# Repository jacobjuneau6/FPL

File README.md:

# FPL
FPL is a FPGA based board that runs linux and provides many digital interfaces.
# WHY
I have always wanted to have a benchtop device that can probe I2C,SPI and uart devices all ath the same time. In addition, I have always wanted to mess around with and use an FPGA.
# PCB

# BOM
| Name | Purpose | Quantity | Total Cost (USD) | Link | Distributor |
| --- | --- | --- | --- | --- | --- |
| 50g Solder Paste | To solder the componets to the board | 1 | 7.34 | https://www.aliexpress.com/item/3256809620386958.html?spm=a2g0o.cart.0.0.202b38daefHo7C&mp=1&pdp_npi=6%40dis%21USD%21USD%2015.29%21USD%207.34%21%21USD%207.34%21%21%21%402103129f17757943610901426e699a%2112000050236831009%21ct%21US%216291447553%21%211%210%21 | Aliexpres |
| FT232H USB -> Bridge | allows programming and debugging the fpga before the core starts | 1 | 7.72 | https://www.aliexpress.com/item/3256810218473690.html?spm=a2g0o.cart.0.0.202b38daefHo7C&mp=1&pdp_npi=6%40dis%21USD%21USD%2015.44%21USD%207.72%21%21USD%207.72%21%21%21%402103129f17757943610901426e699a%2112000052298998974%21ct%21US%216291447553%21%211%210%21 | Aliexpress |
| M-F Dupont Cable | to connect debugger and peripherals | 1 | 2.27 | https://www.aliexpress.com/item/3256803454873245.html?spm=a2g0o.cart.0.0.202b38daefHo7C&mp=1&pdp_npi=6%40dis%21USD%21USD%202.28%21USD%202.27%21%21USD%202.27%21%21%21%402103129f17757943610901426e699a%2112000026613929403%21ct%21US%216291447553%21%211%210%21&pdp_ext_f=%7B%22cart2PdpParams%22%3A%7B%22pdpBusinessMode%22%3A%22retail%22%7D%7D | Aliexpress |
| F-F dupont cable | to wire up debugger and peripherals | 1 | 2.06 | https://www.aliexpress.com/item/3256803454873245.html?spm=a2g0o.cart.0.0.202b38daefHo7C&mp=1&pdp_npi=6%40dis%21USD%21USD%202.07%21USD%202.06%21%21USD%202.06%21%21%21%402103129f17757943610901426e699a%2112000026613929398%21ct%21US%216291447553%21%211%210%21&pdp_ext_f=%7B%22cart2PdpParams%22%3A%7B%22pdpBusinessMode%22%3A%22retail%22%7D%7D | Aliexpress |
| solder paste scraper | to apply the solder paste | 5 | 3.61 | https://www.aliexpress.com/item/3256807243226858.html?spm=a2g0o.cart.0.0.202b38daefHo7C&mp=1&pdp_npi=6%40dis%21USD%21USD%203.61%21USD%203.61%21%21USD%203.61%21%21%21%402103129f17757943610901426e699a%2112000056533716799%21ct%21US%216291447553%21%211%210%21 | Aliexpress |
| JLCPCB Stencils | to make assembly easier | 2 | 6.09 |  | JLCPCB |
| JLCPCB PCBs | Holds all components | 5 | 7.00 |  | JLCPCB |
| MicroSD card holder | storage | 1 | 1.57 | https://www.digikey.com/en/products/detail/hirose-electric-co-ltd/DM3CS-SF/2602739?s=N4IgTCBcDaIBICUCMBOA7GAwgFQLQDkAREAXQF8g | Digikey |
| USB-C connector | data transfer | 1 | 2.99 | https://www.digikey.com/en/products/detail/hirose-electric-co-ltd/CX90BW1-24P1/22566049?s=N4IgTCBcDa4GwFoDCANAnABgEIHUCMCYALAAp5IAqCAcgCIgC6AvkA | Digikey |
| Ethernet Jack | data transfer | 1 | 4.42 | https://www.digikey.com/en/products/detail/te-connectivity-amp-connectors/2041411-1/7039302?s=N4IgTCBcDaIIIEYDMBWAbKgwgFQLQDkAREAXQF8g | Digikey |
| Mosfet | reset the sd card | 1 | 0.28 | https://www.digikey.com/en/products/detail/infineon-technologies/BSS84PH6327XTSA2/5413661?s=N4IgTCBcDaIEIGUEA4AsAFAEgNgMxgHYANAFQQEEwBhEgWgDkAREAXQF8g | Digikey |
| 10K resistors | filtering | 18 | 0.00 |  |  |
| 5.1K resistors | filtering | 2 | 0.20 | https://www.digikey.com/en/products/detail/yageo/RC0402FR-075K1L/726624?s=N4IgTCBcDaIMwEYEFoCsA6BAGA0gGQCUBhAFWQDkAREAXQF8g | Digikey |
| Infineon S80KS5123GABHV020 | RAM | 1 | 11.59 | https://www.digikey.com/en/products/detail/infineon-technologies/S80KS5123GABHV020/15965285 | Digikey |
| tactile button | fpga reset | 1 | 0.24 | https://www.digikey.com/en/products/detail/omron-electronics-inc-emc-div/B3F-1000/33150 | Digikey |
| Dip switches | fpga confiuration | 1 | 3.41 | https://www.digikey.com/en/products/detail/w%C3%BCrth-elektronik/416131160803/3174527?s=N4IgTCBcDaIOwGYwFoAsBGAbOh6sAYAOfBAYQBVkA5AERAF0BfIA | Digikey |
| FPGA | main chip | 1 | 21.78 | https://www.digikey.com/en/products/detail/lattice-semiconductor-corporation/LFE5U-25F-6BG256C/9553918 | Digikey |
| Ethernet Interface | data transfer | 1 | 1.03 | https://www.digikey.com/en/products/detail/microchip-technology/LAN8720A-CP-TR/3872109 | Digikey |
| 1V2 LDO | power regulation | 1 | 0.39 | https://www.digikey.com/en/products/detail/stmicroelectronics/LD1117S12CTR/1880164?s=N4IgTCBcDaIDIBECMKDsBlJYDCAVASiALoC%2BQA | Digikey |
| CP2102 | usb>uart | 1 | 4.14 | https://www.digikey.com/en/products/detail/silicon-labs/CP2102N-A02-GQFN24R/9863479?s=N4IgTCBcDaIMxwGwFoCsAOTyCMyByAIiALoC%2BQA | Digikey |
| SPI Flash | storage | 1 | 2.31 | https://www.digikey.com/en/products/detail/winbond-electronics/W25Q128JVSIQ-TR/5803944?s=N4IgTCBcDa4KwDYC0B1McCKBGMAOAUgGoDKAkhgCoBKAwhUgHIAiIAugL5A | Digikey |
| 25MHZ clock | clock | 1 | 0.99 | https://www.digikey.com/en/products/detail/abracon-llc/ASE-25-000MHZ-L-C-T/1236885?s=N4IgTCBcDaIKwGY4FoCCBlAosscB0ADEQLIASAWsgDLIDCyAKrQ8gHIAiIAugL5A | Digikey |
| 25MHZ Parrallel clock | ethernet | 1 | 1.02 | https://www.digikey.com/en/products/detail/ecs-inc/ECS-250-18-23A-EN-TR/2213748?s=N4IgTCBcDaIBoGECMA2A7EhAVAtAOQBEQBdAXyA | Digikey |
| 4.7K resistors | filtering | 3 | 0.30 | https://www.digikey.com/en/products/detail/yageo/RC0402JR-074K7L/726477?s=N4IgTCBcDaIMwEYEFoAsA6A7AaQFICUBhAFWQDkAREAXQF8g | Digikey |
| 0.1uF capacitor | power filtering | 4 | 0.32 | https://www.digikey.com/en/products/detail/murata-electronics/GRM022D80G104ME15L/5027471?s=N4IgTCBcDaICwE4AMBaAjEgzADgGzpQDkAREAXQF8g | Digikey |
| 22pF capacitor | power filtering | 2 | 0.16 | https://www.digikey.com/en/products/detail/yageo/CC0402JRNPO9BN220/302752 | Digikey |
| 3V3 LDO | power regulation | 1 | 0.32 | https://www.digikey.com/en/products/detail/stmicroelectronics/LD1117S33CTR/585765?s=N4IgTCBcDaIDIBECMKDsBlAzJgwgFQCUQBdAXyA | Digikey |
| 2V5 LDO | power regulation | 1 | 0.49 | https://www.digikey.com/en/products/detail/stmicroelectronics/LD1117S25CTR/585764?s=N4IgTCBcDaIDIBECMKDsBlMBWAwgFQCUQBdAXyA | Digikey |
| 1V8 LDO | power regulation | 1 | 0.42 | https://www.digikey.com/en/products/detail/stmicroelectronics/LD1117S18TR/1038359?s=N4IgTCBcDaIDIBECMKDsBlJAOAKgJRAF0BfIA | Digikey |
| green LED | indication light | 2 | 0.54 | https://www.digikey.com/en/products/detail/w%C3%BCrth-elektronik/155124GS73200A/8557187?s=N4IgTCBcDaIOwGYwFoCMYAMYWuQOQBEQBdAXyA | Digikey |

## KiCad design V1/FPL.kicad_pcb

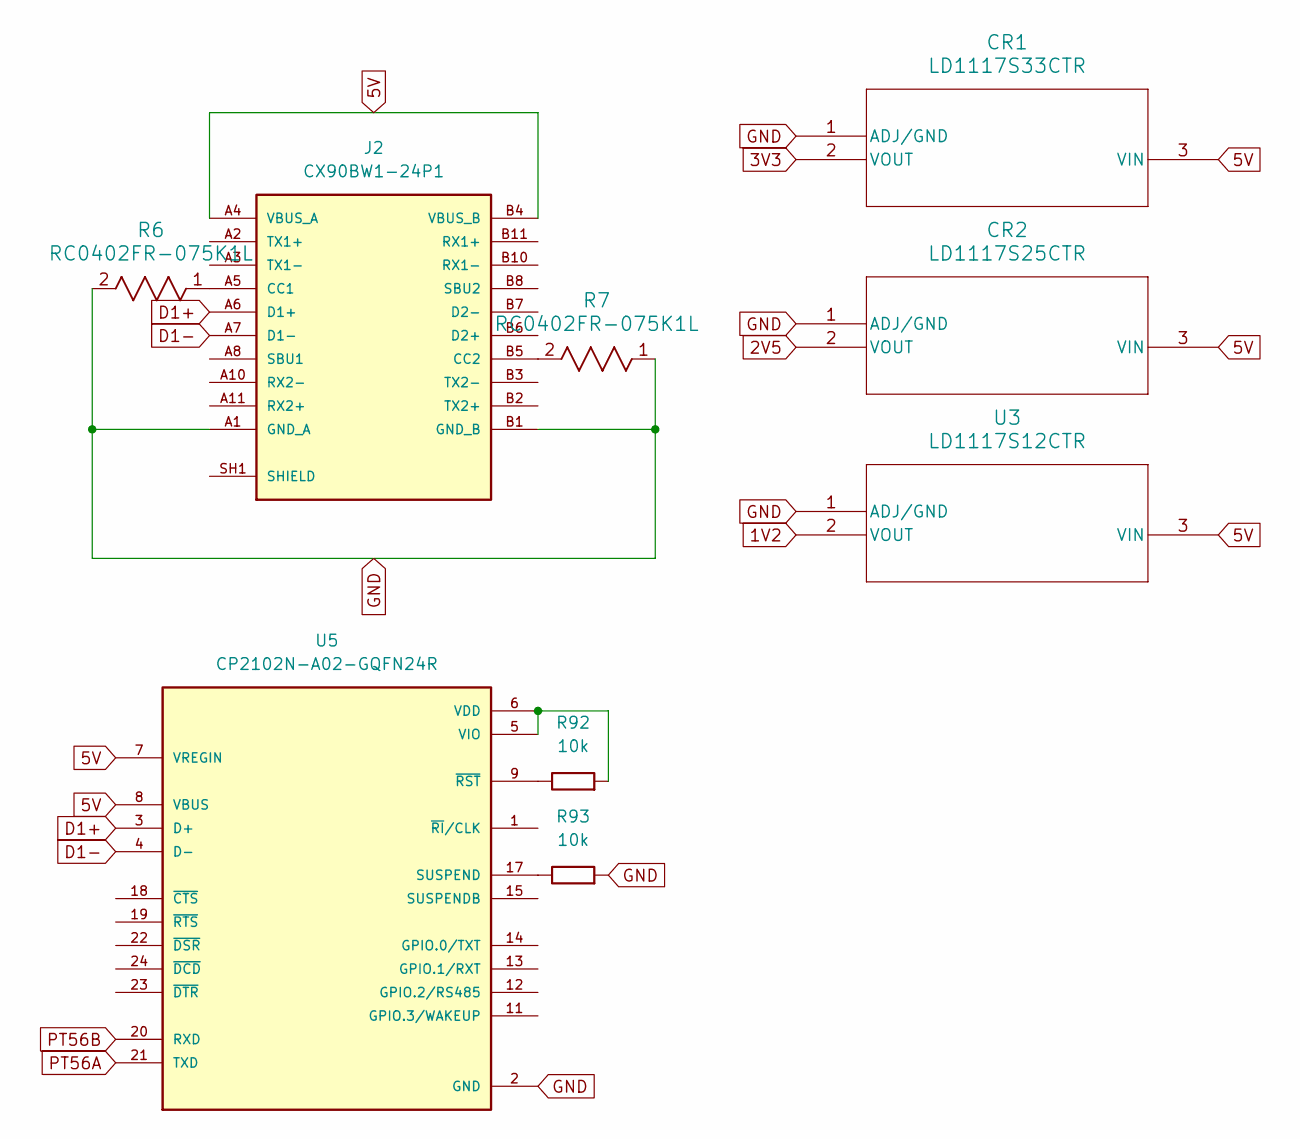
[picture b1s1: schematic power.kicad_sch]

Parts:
CR1: LD1117S33CTR; SOT-223_STM; DigiKey_Part_Number LD1117S33CTR
CR2: LD1117S25CTR; SOT-223_STM; DigiKey_Part_Number LD1117S25CTR
J2: CX90BW1-24P1; HIROSE_CX90BW1-24P1; PARTREV 24.05.01; DigiKey_Part_Number 26-CX90BW1-24P1CT-ND
R6, R7: RC0402FR-075K1L; RC0402N_YAG; DigiKey_Part_Number 311-5.10KLRCT-ND
R92, R93: 10k; R_Axial_DIN0207_L6.3mm_D2.5mm_P10.16mm_Horizontal; DigiKey_Part_Number N/A
U3: LD1117S12CTR; SOT-223_STM; DigiKey_Part_Number LD1117S12CTR
U5: CP2102N-A02-GQFN24R; QFN50P400X400X80-25N; PARTREV 1.3; DigiKey_Part_Number 336-5888-1-ND

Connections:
1V2: U3.2 (VOUT); also elsewhere on the board
2V5: CR2.2 (VOUT); also elsewhere on the board
3V3: CR1.2 (VOUT); also elsewhere on the board
5V: CR1.3 (VIN), CR2.3 (VIN), J2.A4 (VBUS_A), J2.A9 (VBUS_A), J2.B4 (VBUS_B), J2.B9 (VBUS_B), U3.3 (VIN), U5.7 (VREGIN), U5.8 (VBUS); also elsewhere on the board
D1+: J2.A6 (D1+), U5.3 (D+)
D1-: J2.A7 (D1-), U5.4 (D-)
GND: CR1.1 (ADJ/GND), CR2.1 (ADJ/GND), J2.A1 (GND_A), J2.A12 (GND_A), J2.B1 (GND_B), J2.B12 (GND_B), R6.2, R7.1, R93.1, U3.1 (ADJ/GND), U5.2 (GND), U5.25 (GND); also elsewhere on the board
unnamed: J2.A5 (CC1), R6.1
unnamed: J2.B5 (CC2), R7.2
unnamed: J2.SH1 (SHIELD), J2.SH2 (SHIELD), J2.SH3 (SHIELD), J2.SH4 (SHIELD)
unnamed: R93.2, U5.17 (SUSPEND)
unnamed: R92.1, U5.5 (VIO), U5.6 (VDD)
unnamed: R92.2, U5.9 (~RST)
PT56A: U5.21 (TXD); also elsewhere on the board
PT56B: U5.20 (RXD); also elsewhere on the board

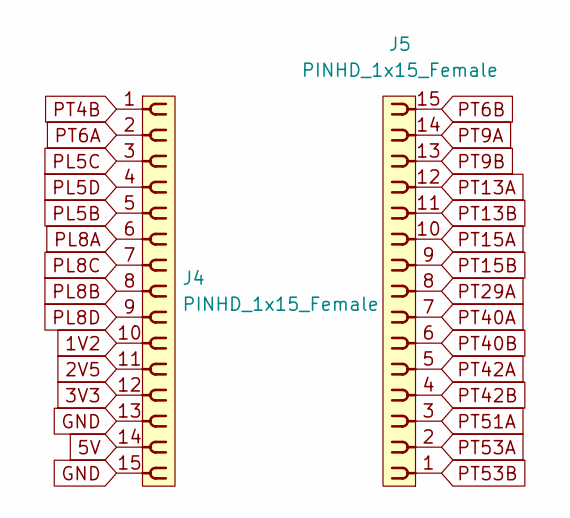
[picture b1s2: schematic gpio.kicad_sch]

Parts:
J4, J5: PINHD_1x15_Female; PinSocket_1x15_P2.54mm_Vertical

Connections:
1V2: J4.10; also elsewhere on the board
2V5: J4.11; also elsewhere on the board
3V3: J4.12; also elsewhere on the board
5V: J4.14; also elsewhere on the board
GND: J4.13, J4.15; also elsewhere on the board
PL5B: J4.5; also elsewhere on the board
PL5C: J4.3; also elsewhere on the board
PL5D: J4.4; also elsewhere on the board
PL8A: J4.6; also elsewhere on the board
PL8B: J4.8; also elsewhere on the board
PL8C: J4.7; also elsewhere on the board
PL8D: J4.9; also elsewhere on the board
PT4B: J4.1; also elsewhere on the board
PT6A: J4.2; also elsewhere on the board
PT6B: J5.15; also elsewhere on the board
PT9A: J5.14; also elsewhere on the board
PT9B: J5.13; also elsewhere on the board
PT13A: J5.12; also elsewhere on the board
PT13B: J5.11; also elsewhere on the board
PT15A: J5.10; also elsewhere on the board
PT15B: J5.9; also elsewhere on the board
PT29A: J5.8; also elsewhere on the board
PT40A: J5.7; also elsewhere on the board
PT40B: J5.6; also elsewhere on the board
PT42A: J5.5; also elsewhere on the board
PT42B: J5.4; also elsewhere on the board
PT51A: J5.3; also elsewhere on the board
PT53A: J5.2; also elsewhere on the board
PT53B: J5.1; also elsewhere on the board

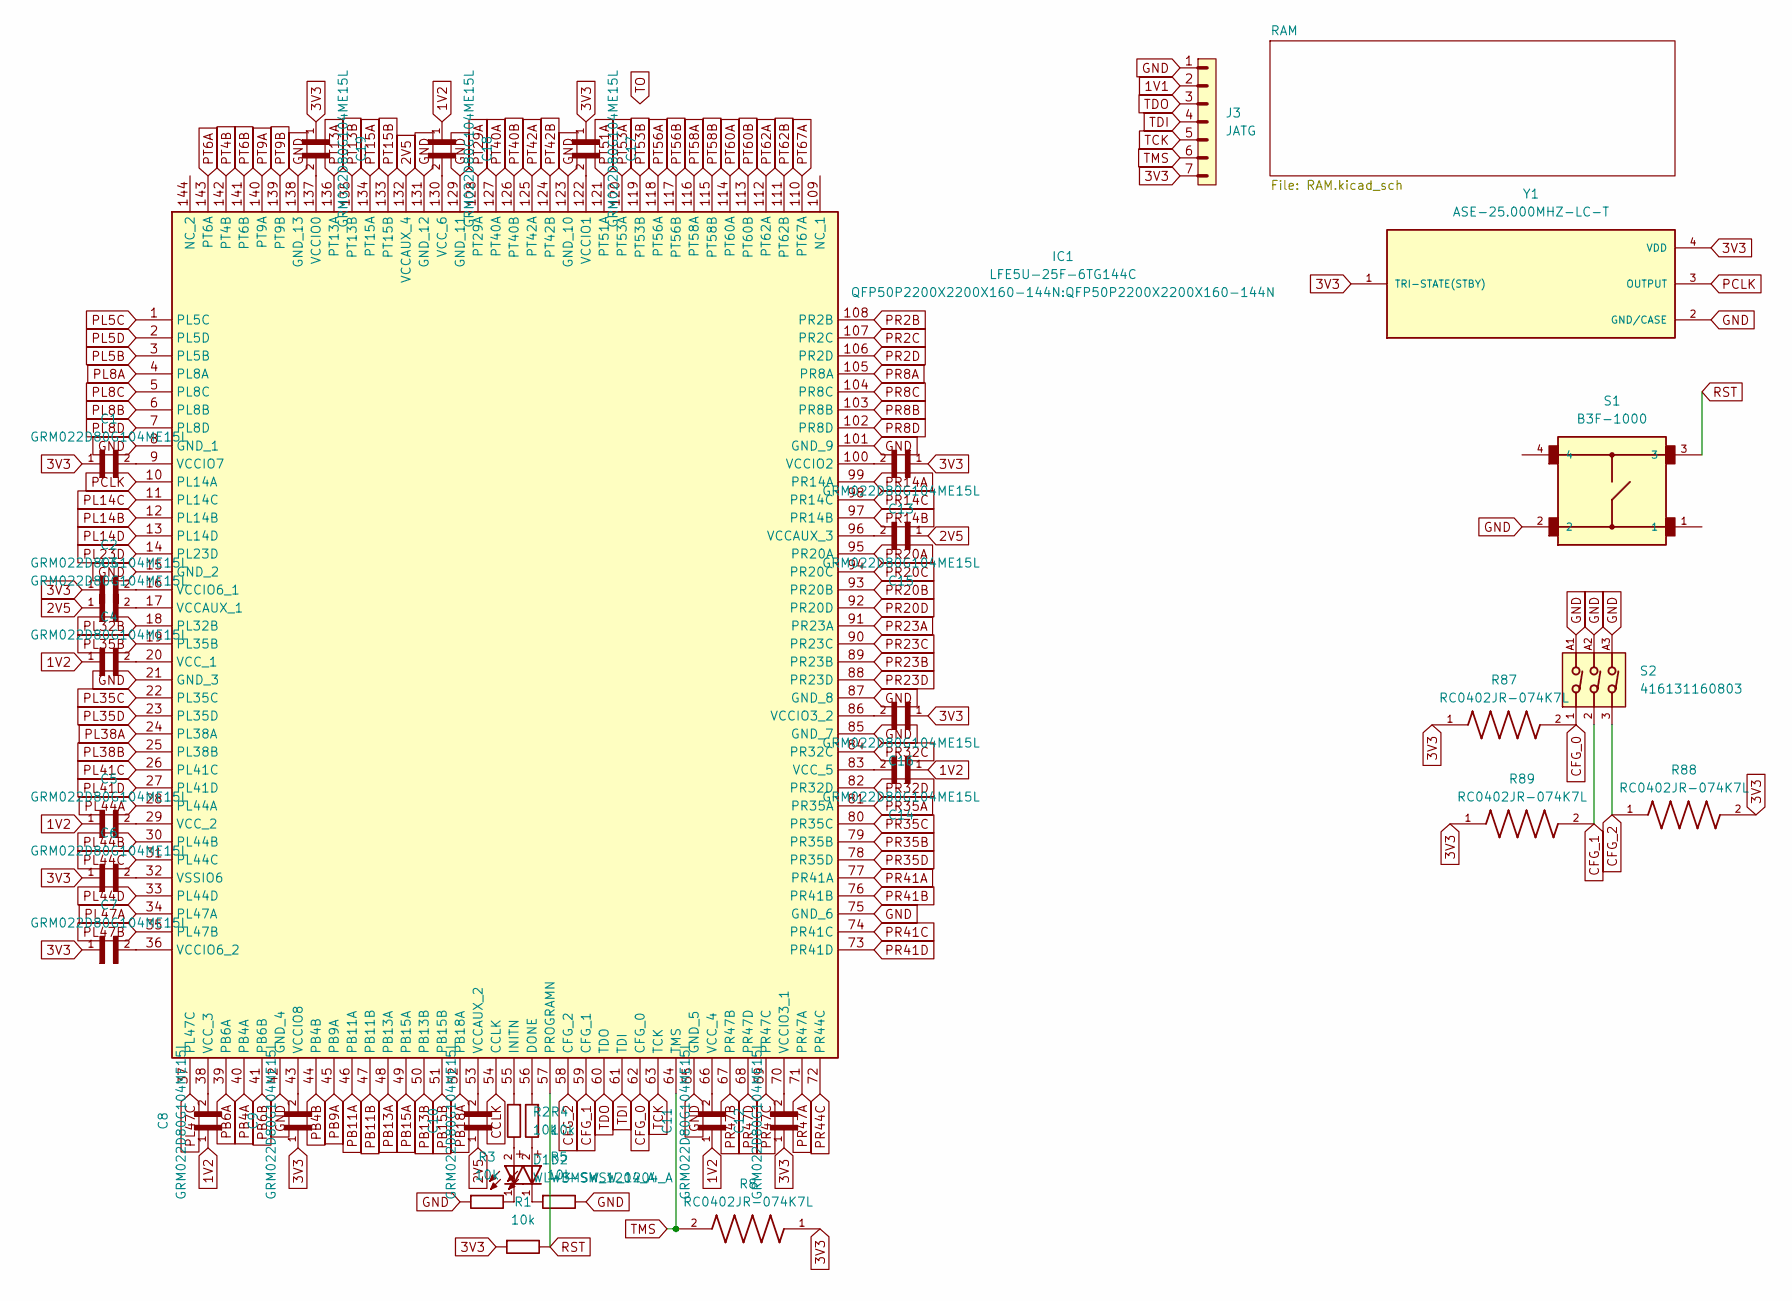
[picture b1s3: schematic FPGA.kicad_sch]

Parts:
C1, C2, C3, C4, C5, C6, C7, C8, C9, C10, C11, C12, C13, C14, C15, C16, C17, C18, C19: GRM022D80G104ME15L; CAPC0402X22N; DigiKey_Part_Number 490-10386-1-ND
D1, D2: WL-SMSW_1204_A; DigiKey_Part_Number 732-12022-1-ND
IC1: LFE5U-25F-6TG144C; QFP50P2200X2200X160-144N; Manufacturer_Part_Number LFE5U-25F-6TG144C; Mouser Part Number 842-LFE5U25F6TG144C
J3: JATG; PinHeader_1x07_P2.54mm_Vertical
R1, R2, R3, R4, R5: 10k; R_Axial_DIN0207_L6.3mm_D2.5mm_P10.16mm_Horizontal; DigiKey_Part_Number N/A
R8: RC0402JR-074K7L; RESC1005X40N; DigiKey_Part_Number 311-4.7KJRCT-ND
R87, R88, R89: RC0402JR-074K7L; RC0402N_YAG; DigiKey_Part_Number 311-4.7KJRCT-ND
S1: B3F-1000; SW_B3F-1000; DigiKey_Part_Number SW400-ND
S2: 416131160803; DigiKey_Part_Number 732-416131160803CT-ND
Y1: ASE-25.000MHZ-LC-T; XTAL_ASE-25.000MHZ-LC-T; PARTREV 02-18-22; DigiKey_Part_Number 535-ASE-25.000MHZ-L-C-TCT-ND

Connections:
1V1: J3.2
1V2: C4.1, C5.1, C8.1, C11.1, C14.1, C18.1; also elsewhere on the board
2V5: C3.1, C10.1, C15.1, IC1.132 (VCCAUX_4); also elsewhere on the board
3V3: C1.1, C2.1, C6.1, C7.1, C9.1, C12.1, C13.1, C16.1, C17.1, C19.1, J3.7, R1.1, R8.1, R87.1, R88.2, R89.1, Y1.1 (TRI-STATE(STBY)), Y1.4 (VDD); also elsewhere on the board
CCLK: IC1.54 (CCLK)
CFG_0: IC1.62 (CFG_0), R87.2, S2.1
CFG_1: IC1.59 (CFG_1), R89.2, S2.2
CFG_2: IC1.58 (CFG_2), R88.1, S2.3
GND: IC1.8 (GND_1), IC1.15 (GND_2), IC1.21 (GND_3), IC1.42 (GND_4), IC1.65 (GND_5), IC1.75 (GND_6), IC1.85 (GND_7), IC1.87 (GND_8), IC1.101 (GND_9), IC1.123 (GND_10), IC1.129 (GND_11), IC1.131 (GND_12), IC1.138 (GND_13), J3.1, R3.1, R5.2, S1.2, S2.A1, S2.A2, S2.A3, Y1.2 (GND/CASE); also elsewhere on the board
unnamed: D1.1, R3.2
unnamed: D1.2, R2.2
unnamed: D2.1, R5.1
unnamed: D2.2, R4.2
unnamed: IC1.56 (DONE), R4.1
unnamed: IC1.55 (INITN), R2.1
unnamed: C3.2, IC1.17 (VCCAUX_1)
unnamed: C10.2, IC1.53 (VCCAUX_2)
unnamed: C15.2, IC1.96 (VCCAUX_3)
unnamed: C19.2, IC1.137 (VCCIO0)
unnamed: C17.2, IC1.122 (VCCIO1)
unnamed: C13.2, IC1.100 (VCCIO2)
unnamed: C12.2, IC1.70 (VCCIO3_1)
unnamed: C16.2, IC1.86 (VCCIO3_2)
unnamed: C2.2, IC1.16 (VCCIO6_1)
unnamed: C7.2, IC1.36 (VCCIO6_2)
unnamed: C1.2, IC1.9 (VCCIO7)
unnamed: C9.2, IC1.43 (VCCIO8)
unnamed: C4.2, IC1.20 (VCC_1)
unnamed: C5.2, IC1.29 (VCC_2)
unnamed: C8.2, IC1.38 (VCC_3)
unnamed: C11.2, IC1.66 (VCC_4)
unnamed: C14.2, IC1.83 (VCC_5)
unnamed: C18.2, IC1.130 (VCC_6)
unnamed: C6.2, IC1.32 (VSSIO6)
PB4A: IC1.40 (PB4A); also elsewhere on the board
PB4B: IC1.44 (PB4B); also elsewhere on the board
PB6A: IC1.39 (PB6A); also elsewhere on the board
PB6B: IC1.41 (PB6B); also elsewhere on the board
PB9A: IC1.45 (PB9A); also elsewhere on the board
PB11A: IC1.46 (PB11A); also elsewhere on the board
PB11B: IC1.47 (PB11B); also elsewhere on the board
PB13A: IC1.48 (PB13A); also elsewhere on the board
PB13B: IC1.50 (PB13B); also elsewhere on the board
PB15A: IC1.49 (PB15A); also elsewhere on the board
PB15B: IC1.51 (PB15B); also elsewhere on the board
PB18A: IC1.52 (PB18A); also elsewhere on the board
PCLK: IC1.10 (PL14A), Y1.3 (OUTPUT)
PL5B: IC1.3 (PL5B); also elsewhere on the board
PL5C: IC1.1 (PL5C); also elsewhere on the board
PL5D: IC1.2 (PL5D); also elsewhere on the board
PL8A: IC1.4 (PL8A); also elsewhere on the board
PL8B: IC1.6 (PL8B); also elsewhere on the board
PL8C: IC1.5 (PL8C); also elsewhere on the board
PL8D: IC1.7 (PL8D); also elsewhere on the board
PL14B: IC1.12 (PL14B); also elsewhere on the board
PL14C: IC1.11 (PL14C); also elsewhere on the board
PL14D: IC1.13 (PL14D); also elsewhere on the board
PL23D: IC1.14 (PL23D); also elsewhere on the board
PL32B: IC1.18 (PL32B); also elsewhere on the board
PL35B: IC1.19 (PL35B); also elsewhere on the board
PL35C: IC1.22 (PL35C); also elsewhere on the board
PL35D: IC1.23 (PL35D); also elsewhere on the board
PL38A: IC1.24 (PL38A); also elsewhere on the board
PL38B: IC1.25 (PL38B); also elsewhere on the board
PL41C: IC1.26 (PL41C); also elsewhere on the board
PL41D: IC1.27 (PL41D); also elsewhere on the board
PL44A: IC1.28 (PL44A); also elsewhere on the board
PL44B: IC1.30 (PL44B); also elsewhere on the board
PL44C: IC1.31 (PL44C); also elsewhere on the board
PL44D: IC1.33 (PL44D); also elsewhere on the board
PL47A: IC1.34 (PL47A); also elsewhere on the board
PL47B: IC1.35 (PL47B); also elsewhere on the board
PL47C: IC1.37 (PL47C); also elsewhere on the board
PR2B: IC1.108 (PR2B); also elsewhere on the board
PR2C: IC1.107 (PR2C); also elsewhere on the board
PR2D: IC1.106 (PR2D); also elsewhere on the board
PR8A: IC1.105 (PR8A); also elsewhere on the board
PR8B: IC1.103 (PR8B); also elsewhere on the board
PR8C: IC1.104 (PR8C); also elsewhere on the board
PR8D: IC1.102 (PR8D); also elsewhere on the board
PR14A: IC1.99 (PR14A); also elsewhere on the board
PR14B: IC1.97 (PR14B); also elsewhere on the board
PR14C: IC1.98 (PR14C); also elsewhere on the board
PR20A: IC1.95 (PR20A); also elsewhere on the board
PR20B: IC1.93 (PR20B); also elsewhere on the board
PR20C: IC1.94 (PR20C); also elsewhere on the board
PR20D: IC1.92 (PR20D); also elsewhere on the board
PR23A: IC1.91 (PR23A); also elsewhere on the board
PR23B: IC1.89 (PR23B); also elsewhere on the board
PR23C: IC1.90 (PR23C); also elsewhere on the board
PR23D: IC1.88 (PR23D)
PR32C: IC1.84 (PR32C); also elsewhere on the board
PR32D: IC1.82 (PR32D); also elsewhere on the board
PR35A: IC1.81 (PR35A); also elsewhere on the board
PR35B: IC1.79 (PR35B); also elsewhere on the board
PR35C: IC1.80 (PR35C); also elsewhere on the board
PR35D: IC1.78 (PR35D); also elsewhere on the board
PR41A: IC1.77 (PR41A); also elsewhere on the board
PR41B: IC1.76 (PR41B); also elsewhere on the board
PR41C: IC1.74 (PR41C); also elsewhere on the board
PR41D: IC1.73 (PR41D); also elsewhere on the board
PR44C: IC1.72 (PR44C); also elsewhere on the board
PR47A: IC1.71 (PR47A); also elsewhere on the board
PR47B: IC1.67 (PR47B); also elsewhere on the board
PR47C: IC1.69 (PR47C); also elsewhere on the board
PR47D: IC1.68 (PR47D); also elsewhere on the board
PT4B: IC1.142 (PT4B); also elsewhere on the board
PT6A: IC1.143 (PT6A); also elsewhere on the board
PT6B: IC1.141 (PT6B); also elsewhere on the board
PT9A: IC1.140 (PT9A); also elsewhere on the board
PT9B: IC1.139 (PT9B); also elsewhere on the board
PT13A: IC1.136 (PT13A); also elsewhere on the board
PT13B: IC1.135 (PT13B); also elsewhere on the board
PT15A: IC1.134 (PT15A); also elsewhere on the board
PT15B: IC1.133 (PT15B); also elsewhere on the board
PT29A: IC1.128 (PT29A); also elsewhere on the board
PT40A: IC1.127 (PT40A); also elsewhere on the board
PT40B: IC1.126 (PT40B); also elsewhere on the board
PT42A: IC1.125 (PT42A); also elsewhere on the board
PT42B: IC1.124 (PT42B); also elsewhere on the board
PT51A: IC1.121 (PT51A); also elsewhere on the board
PT53A: IC1.120 (PT53A); also elsewhere on the board
PT53B: IC1.119 (PT53B); also elsewhere on the board
PT56A: IC1.118 (PT56A); also elsewhere on the board
PT56B: IC1.117 (PT56B); also elsewhere on the board
PT58A: IC1.116 (PT58A); also elsewhere on the board
PT58B: IC1.115 (PT58B); also elsewhere on the board
PT60A: IC1.114 (PT60A); also elsewhere on the board
PT60B: IC1.113 (PT60B); also elsewhere on the board
PT62A: IC1.112 (PT62A); also elsewhere on the board
PT62B: IC1.111 (PT62B); also elsewhere on the board
PT67A: IC1.110 (PT67A); also elsewhere on the board
RST: IC1.57 (PROGRAMN), R1.2, S1.3
TCK: IC1.63 (TCK), J3.5
TDI: IC1.61 (TDI), J3.4
TDO: IC1.60 (TDO), J3.3
TMS: IC1.64 (TMS), J3.6, R8.2

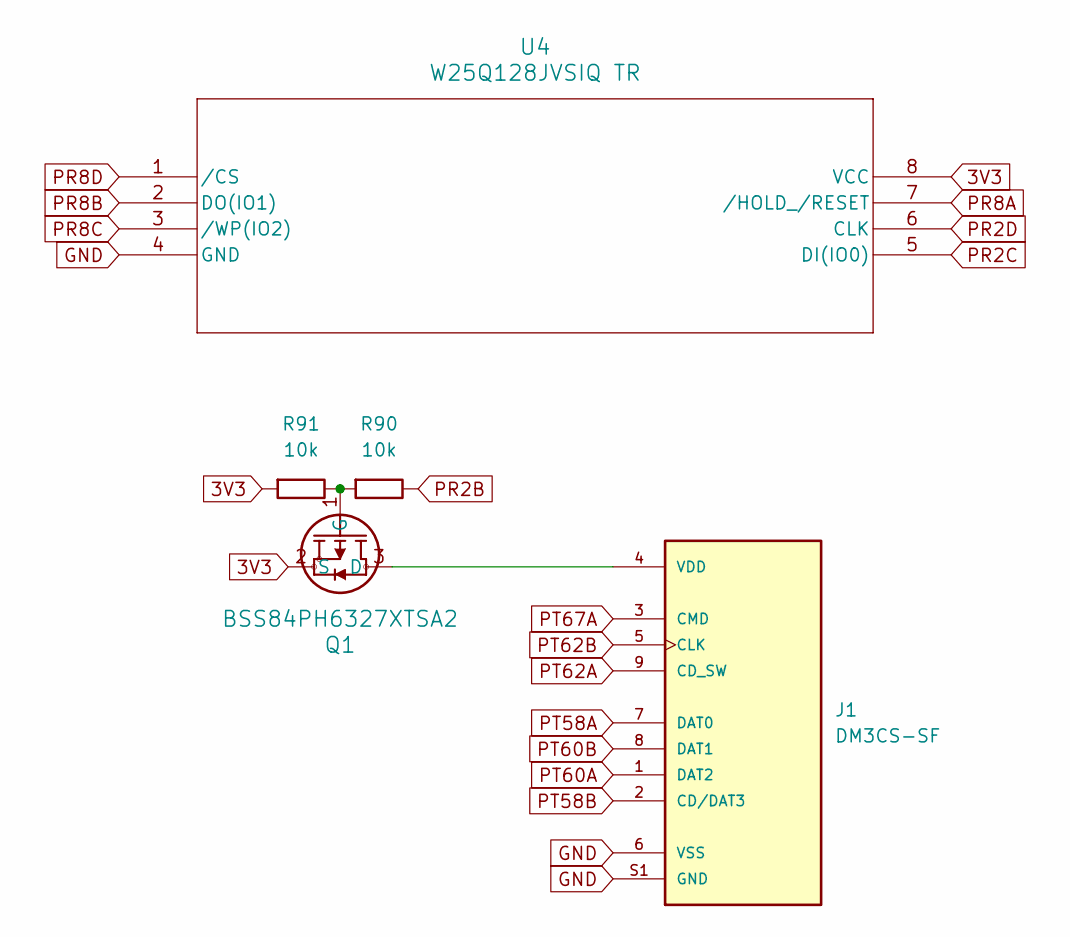
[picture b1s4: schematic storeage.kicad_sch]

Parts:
J1: DM3CS-SF; HRS_DM3CS-SF; PARTREV n/a; DigiKey_Part_Number HR1972CT-ND
Q1: BSS84PH6327XTSA2; SOT23_BSS84_INF; DigiKey_Part_Number BSS84PH6327XTSA2CT-ND
R90, R91: 10k; R_Axial_DIN0207_L6.3mm_D2.5mm_P10.16mm_Horizontal; DigiKey_Part_Number N/A
U4: W25Q128JVSIQ TR; SOIC_208MIL_WIN; DigiKey_Part_Number 256-W25Q128JVSIQTRCT-ND

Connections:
3V3: Q1.2 (S), R91.1, U4.8 (VCC); also elsewhere on the board
GND: J1.6 (VSS), J1.S1 (GND), J1.S2 (GND), J1.S3 (GND), J1.S5 (GND), U4.4 (GND); also elsewhere on the board
unnamed: J1.4 (VDD), Q1.3 (D)
unnamed: Q1.1 (G), R90.1, R91.2
PR2B: R90.2; also elsewhere on the board
PR2C: U4.5 (DI(IO0)); also elsewhere on the board
PR2D: U4.6 (CLK); also elsewhere on the board
PR8A: U4.7 (/HOLD_/RESET); also elsewhere on the board
PR8B: U4.2 (DO(IO1)); also elsewhere on the board
PR8C: U4.3 (/WP(IO2)); also elsewhere on the board
PR8D: U4.1 (/CS); also elsewhere on the board
PT58A: J1.7 (DAT0); also elsewhere on the board
PT58B: J1.2 (CD/DAT3); also elsewhere on the board
PT60A: J1.1 (DAT2); also elsewhere on the board
PT60B: J1.8 (DAT1); also elsewhere on the board
PT62A: J1.9 (CD_SW); also elsewhere on the board
PT62B: J1.5 (CLK); also elsewhere on the board
PT67A: J1.3 (CMD); also elsewhere on the board

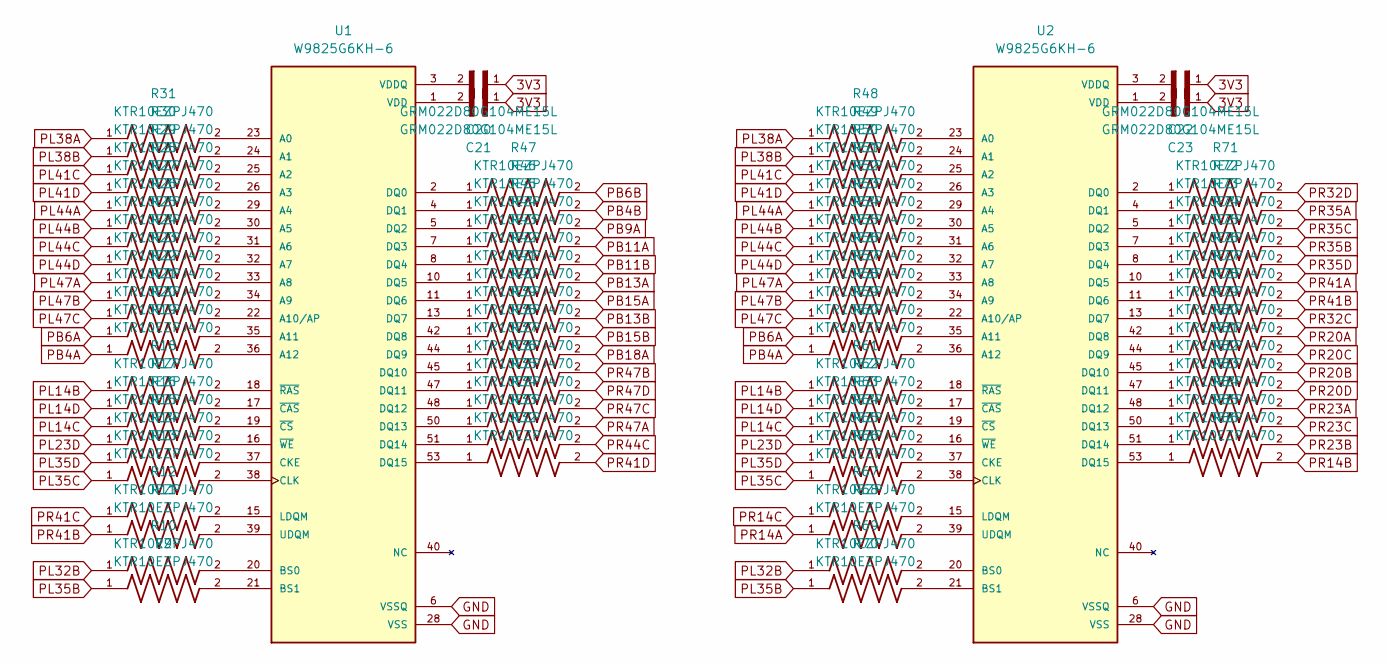
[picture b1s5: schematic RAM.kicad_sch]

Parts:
C20, C21, C22, C23: GRM022D80G104ME15L; CAPC0402X22N; DigiKey_Part_Number 490-10386-1-ND
R9, R10, R11, R12, R13, R14, R15, R16, R17, R18, R19, R20, R21, R22, R23, R24, R25, R26, R27, R28, R29, R30, R31, R32, R33, R34, R35, R36, R37, R38, R39, R40, R41, R42, R43, R44, R45, R46, R47, R48, R49, R50, R51, R52, R53, R54, R55, R56, R57, R58, R59, R60, R61, R62, R63, R64, R65, R66, R67, R68, R69, R70, R71, R72, R73, R74, R75, R76, R77, R78, R79, R80, R81, R82, R83, R84, R85, R86: KTR10EZPJ470; RES_ERJXGNF47R0Y; DigiKey_Part_Number RHM47BCT-ND
U1, U2: W9825G6KH-6; SOP80P1176X120-54N; PARTREV A05; DigiKey_Part_Number W9825G6KH-6-ND

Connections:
3V3: C20.1, C21.1, C22.1, C23.1; also elsewhere on the board
GND: U1.6 (VSSQ), U1.12 (VSSQ), U1.28 (VSS), U1.41 (VSS), U1.46 (VSSQ), U1.52 (VSSQ), U1.54 (VSS), U2.6 (VSSQ), U2.12 (VSSQ), U2.28 (VSS), U2.41 (VSS), U2.46 (VSSQ), U2.52 (VSSQ), U2.54 (VSS); also elsewhere on the board
unnamed: R31.2, U1.23 (A0)
unnamed: R30.2, U1.24 (A1)
unnamed: R29.2, U1.25 (A2)
unnamed: R28.2, U1.26 (A3)
unnamed: R27.2, U1.29 (A4)
unnamed: R26.2, U1.30 (A5)
unnamed: R25.2, U1.31 (A6)
unnamed: R24.2, U1.32 (A7)
unnamed: R23.2, U1.33 (A8)
unnamed: R22.2, U1.34 (A9)
unnamed: R21.2, U1.22 (A10/AP)
unnamed: R20.2, U1.35 (A11)
unnamed: R19.2, U1.36 (A12)
unnamed: R10.2, U1.20 (BS0)
unnamed: R9.2, U1.21 (BS1)
unnamed: R14.2, U1.37 (CKE)
unnamed: R13.2, U1.38 (CLK)
unnamed: R47.1, U1.2 (DQ0)
unnamed: R46.1, U1.4 (DQ1)
unnamed: R45.1, U1.5 (DQ2)
unnamed: R44.1, U1.7 (DQ3)
unnamed: R43.1, U1.8 (DQ4)
unnamed: R42.1, U1.10 (DQ5)
unnamed: R41.1, U1.11 (DQ6)
unnamed: R40.1, U1.13 (DQ7)
unnamed: R39.1, U1.42 (DQ8)
unnamed: R38.1, U1.44 (DQ9)
unnamed: R37.1, U1.45 (DQ10)
unnamed: R36.1, U1.47 (DQ11)
unnamed: R35.1, U1.48 (DQ12)
unnamed: R34.1, U1.50 (DQ13)
unnamed: R33.1, U1.51 (DQ14)
unnamed: R32.1, U1.53 (DQ15)
unnamed: R12.2, U1.15 (LDQM)
unnamed: R11.2, U1.39 (UDQM)
unnamed: R17.2, U1.17 (~CAS)
unnamed: R16.2, U1.19 (~CS)
unnamed: R18.2, U1.18 (~RAS)
unnamed: R15.2, U1.16 (~WE)
unnamed: R48.2, U2.23 (A0)
unnamed: R49.2, U2.24 (A1)
unnamed: R50.2, U2.25 (A2)
unnamed: R51.2, U2.26 (A3)
unnamed: R52.2, U2.29 (A4)
unnamed: R53.2, U2.30 (A5)
unnamed: R54.2, U2.31 (A6)
unnamed: R55.2, U2.32 (A7)
unnamed: R56.2, U2.33 (A8)
unnamed: R57.2, U2.34 (A9)
unnamed: R58.2, U2.22 (A10/AP)
unnamed: R59.2, U2.35 (A11)
unnamed: R60.2, U2.36 (A12)
unnamed: R69.2, U2.20 (BS0)
unnamed: R70.2, U2.21 (BS1)
unnamed: R65.2, U2.37 (CKE)
unnamed: R66.2, U2.38 (CLK)
unnamed: R71.1, U2.2 (DQ0)
unnamed: R72.1, U2.4 (DQ1)
unnamed: R73.1, U2.5 (DQ2)
unnamed: R74.1, U2.7 (DQ3)
unnamed: R75.1, U2.8 (DQ4)
unnamed: R76.1, U2.10 (DQ5)
unnamed: R77.1, U2.11 (DQ6)
unnamed: R78.1, U2.13 (DQ7)
unnamed: R79.1, U2.42 (DQ8)
unnamed: R80.1, U2.44 (DQ9)
unnamed: R81.1, U2.45 (DQ10)
unnamed: R82.1, U2.47 (DQ11)
unnamed: R83.1, U2.48 (DQ12)
unnamed: R84.1, U2.50 (DQ13)
unnamed: R85.1, U2.51 (DQ14)
unnamed: R86.1, U2.53 (DQ15)
unnamed: R67.2, U2.15 (LDQM)
unnamed: R68.2, U2.39 (UDQM)
unnamed: R62.2, U2.17 (~CAS)
unnamed: R63.2, U2.19 (~CS)
unnamed: R61.2, U2.18 (~RAS)
unnamed: R64.2, U2.16 (~WE)
PB4A: R19.1, R60.1; also elsewhere on the board
PB4B: R46.2; also elsewhere on the board
PB6A: R20.1, R59.1; also elsewhere on the board
PB6B: R47.2; also elsewhere on the board
PB9A: R45.2; also elsewhere on the board
PB11A: R44.2; also elsewhere on the board
PB11B: R43.2; also elsewhere on the board
PB13A: R42.2; also elsewhere on the board
PB13B: R40.2; also elsewhere on the board
PB15A: R41.2; also elsewhere on the board
PB15B: R39.2; also elsewhere on the board
PB18A: R38.2; also elsewhere on the board
PL14B: R18.1, R61.1; also elsewhere on the board
PL14C: R16.1, R63.1; also elsewhere on the board
PL14D: R17.1, R62.1; also elsewhere on the board
PL23D: R15.1, R64.1; also elsewhere on the board
PL32B: R10.1, R69.1; also elsewhere on the board
PL35B: R9.1, R70.1; also elsewhere on the board
PL35C: R13.1, R66.1; also elsewhere on the board
PL35D: R14.1, R65.1; also elsewhere on the board
PL38A: R31.1, R48.1; also elsewhere on the board
PL38B: R30.1, R49.1; also elsewhere on the board
PL41C: R29.1, R50.1; also elsewhere on the board
PL41D: R28.1, R51.1; also elsewhere on the board
PL44A: R27.1, R52.1; also elsewhere on the board
PL44B: R26.1, R53.1; also elsewhere on the board
PL44C: R25.1, R54.1; also elsewhere on the board
PL44D: R24.1, R55.1; also elsewhere on the board
PL47A: R23.1, R56.1; also elsewhere on the board
PL47B: R22.1, R57.1; also elsewhere on the board
PL47C: R21.1, R58.1; also elsewhere on the board
PR14A: R68.1; also elsewhere on the board
PR14B: R86.2; also elsewhere on the board
PR14C: R67.1; also elsewhere on the board
PR20A: R79.2; also elsewhere on the board
PR20B: R81.2; also elsewhere on the board
PR20C: R80.2; also elsewhere on the board
PR20D: R82.2; also elsewhere on the board
PR23A: R83.2; also elsewhere on the board
PR23B: R85.2; also elsewhere on the board
PR23C: R84.2; also elsewhere on the board
PR32C: R78.2; also elsewhere on the board
PR32D: R71.2; also elsewhere on the board
PR35A: R72.2; also elsewhere on the board
PR35B: R74.2; also elsewhere on the board
PR35C: R73.2; also elsewhere on the board
PR35D: R75.2; also elsewhere on the board
PR41A: R76.2; also elsewhere on the board
PR41B: R11.1, R77.2; also elsewhere on the board
PR41C: R12.1; also elsewhere on the board
PR41D: R32.2; also elsewhere on the board
PR44C: R33.2; also elsewhere on the board
PR47A: R34.2; also elsewhere on the board
PR47B: R37.2; also elsewhere on the board
PR47C: R35.2; also elsewhere on the board
PR47D: R36.2; also elsewhere on the board

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
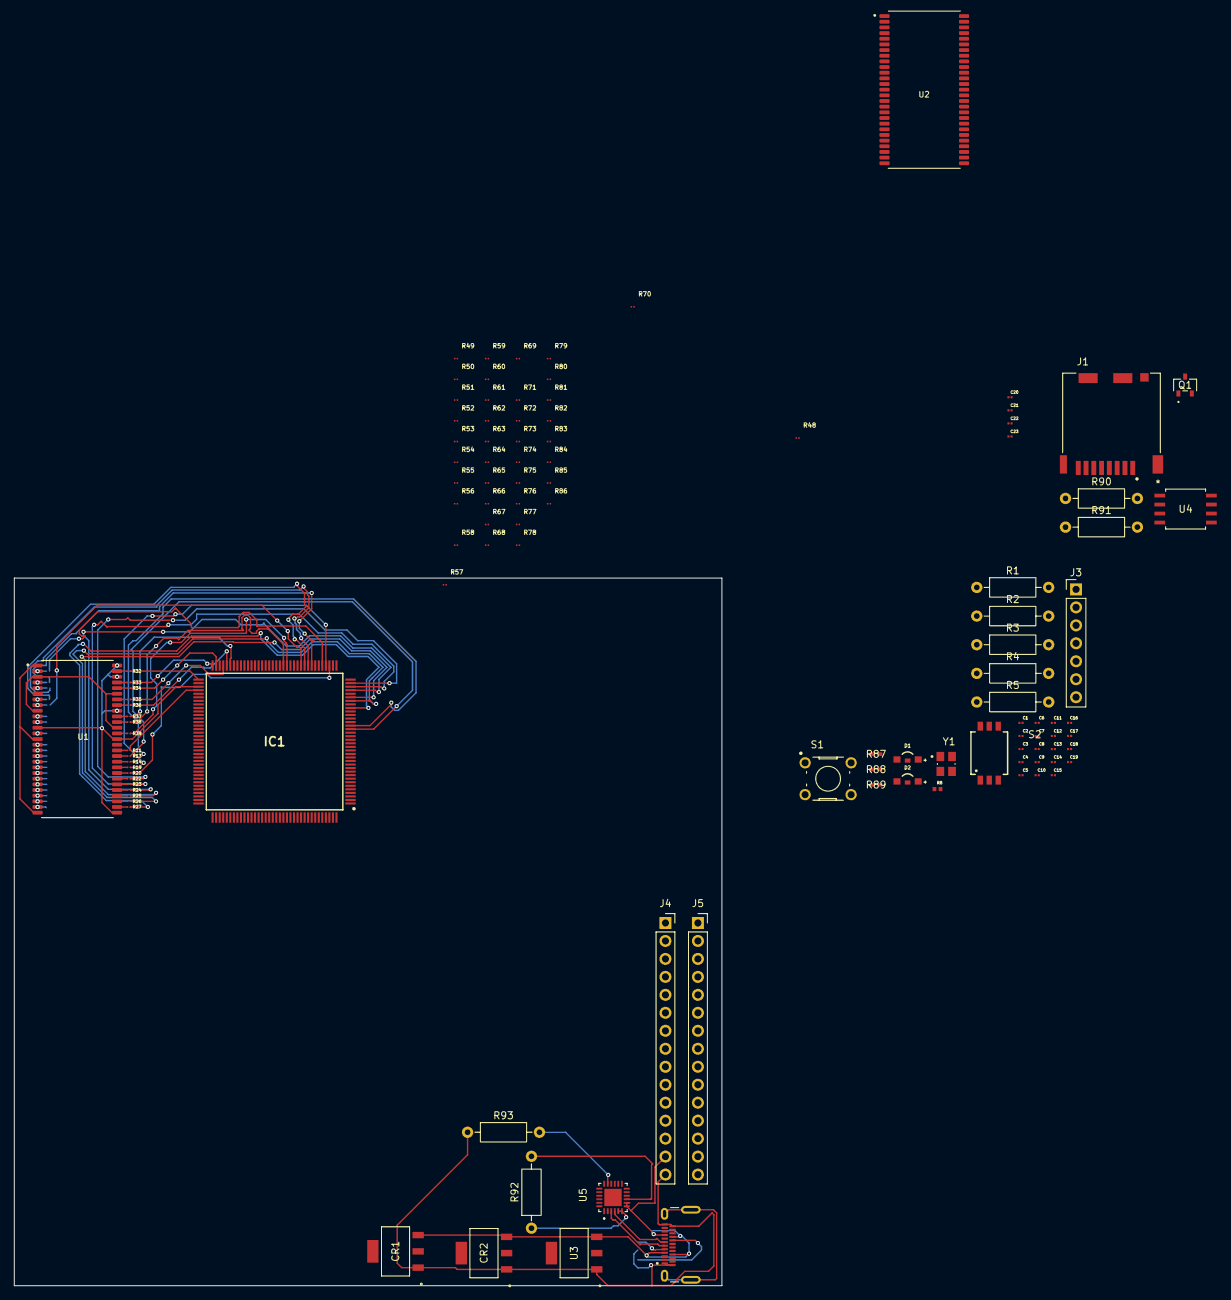
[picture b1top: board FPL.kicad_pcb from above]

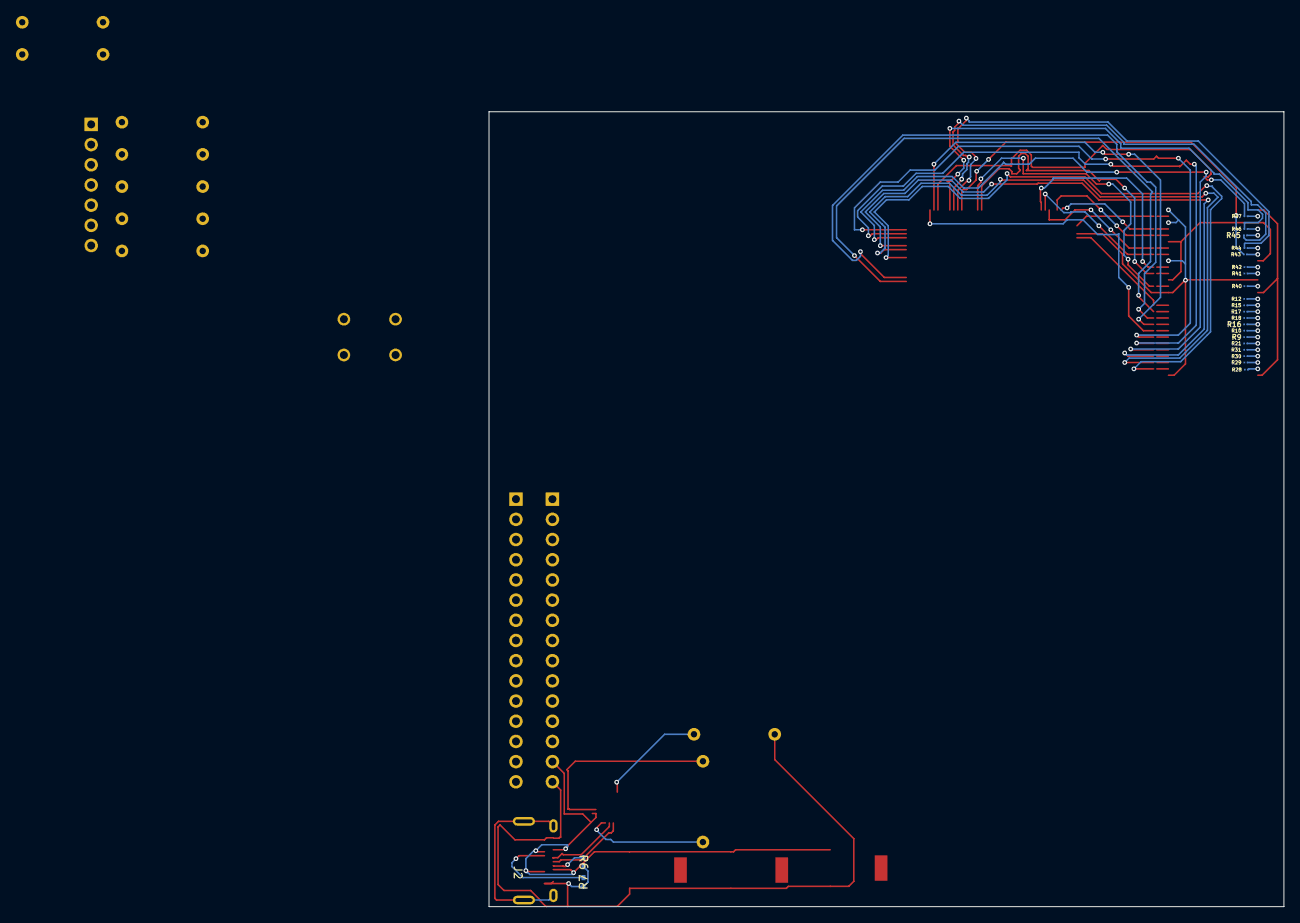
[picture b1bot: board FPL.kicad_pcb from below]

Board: 2 copper layers, 100.0 x 100.0 mm, 135 parts (22 on the bottom side), 225 nets.
